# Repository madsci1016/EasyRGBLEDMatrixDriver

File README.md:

EasyRGBLEDMatrixDriver
======================

Super Easy Arduino based serial backpack driver board for 16 x 32 RGB LED Matrix panels found here: http://www.adafruit.com/products/420

The code and board  design will let you drive a 16x32 RGB LED matrix panel with a serial port, with some limitations. A example sketch for a master controller is included. 

Video Demo:  http://youtu.be/BNk5QkBuxNQ  

FEATURES:
Drive multiple panels off 1 serial port to create larger displays.

LIMITATIONS:
You only get half the resolution of the 16x32 pixel display, only 8x16 which is then scaled to 16x32
Refresh rate is limited by speed and number of displays on the Serial Port

This library runs off of an Arduino Pro/Uno which is NOT powerful enough to display video. It's really meant for animations, text, and Tetris among other things.  

In those pictures only 3 wires are shared by the 4 backpack Arduinos, 5V (Blue), GND (RED) and Data (Yellow) which is connected to the Serial RX of each Arduino (pin 1) the black wire (connected to TX of each Arduino) is not connected between each board. 

The 5th Arduino is the 'Master' and the Data line (Yellow) connects to it's Serial TX pin (Pin 0). 

Arduinos: https://www.sparkfun.com/products/11113
Wire and plug: https://www.sparkfun.com/products/9916

REQUIRES THE FOLLOWING LIBRARIES: 

https://github.com/adafruit/Adafruit-GFX-Library
https://github.com/adafruit/RGB-matrix-Panel
https://github.com/madsci1016/Arduino-EasyTransfer

To wire the display to the backpack arduino (Without my PCB), see:
https://learn.adafruit.com/32x16-32x32-rgb-led-matrix/wiring-the-16x32-matrix

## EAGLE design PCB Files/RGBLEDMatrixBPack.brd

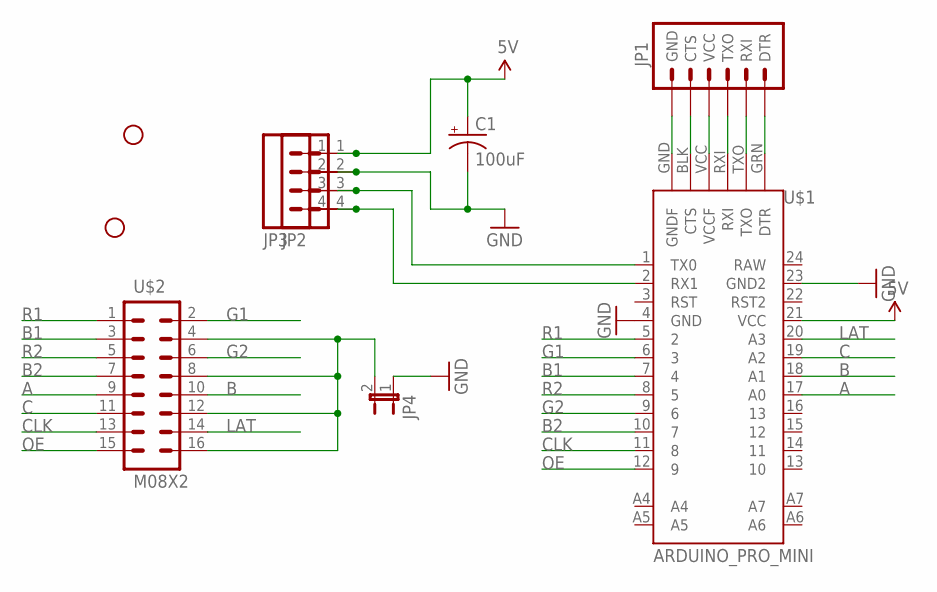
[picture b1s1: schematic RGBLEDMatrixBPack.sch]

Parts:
C1: 100uF; CPOL-RADIAL-100UF-25V
JP1: ARDUINO_SERIAL_PROGRAMPTH; 1X06
JP2, JP3: M04JST-PTH; JST-4-PTH
JP4: JUMPER-2SMD-NO; SJ_2S-NO
STANDOFF1, STANDOFF2: STAND-OFF
U$1: ARDUINO_PRO_MINI
U$2: M08X2; 2X8

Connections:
5V: C1.1 (+), JP2.1, JP3.1, U$1.21 (VCC)
A: U$1.17 (A0), U$2.9
B: U$1.18 (A1), U$2.10
B1: U$1.7 (4), U$2.3
B2: U$1.10 (7), U$2.7
C: U$1.19 (A2), U$2.11
CLK: U$1.11 (8), U$2.13
G1: U$1.6 (3), U$2.2
G2: U$1.9 (6), U$2.6
GND: C1.2 (-), JP2.2, JP3.2, JP4.1, U$1.4 (GND), U$1.23 (GND2)
LAT: U$1.20 (A3), U$2.14
unnamed: JP1.1 (DTR), U$1.GRN (DTR)
unnamed: JP1.2 (RXI), U$1.TXO
unnamed: JP1.3 (TXO), U$1.RXI
unnamed: JP1.4 (VCC), U$1.VCC (VCCF)
unnamed: JP1.5 (CTS), U$1.BLK (CTS)
unnamed: JP1.6 (GND), U$1.GND (GNDF)
unnamed: JP2.4, JP3.4, U$1.2 (RX1)
unnamed: JP2.3, JP3.3, U$1.1 (TX0)
unnamed: JP4.2, U$2.4, U$2.8, U$2.12, U$2.16
OE: U$1.12 (9), U$2.15
R1: U$1.5 (2), U$2.1
R2: U$1.8 (5), U$2.5

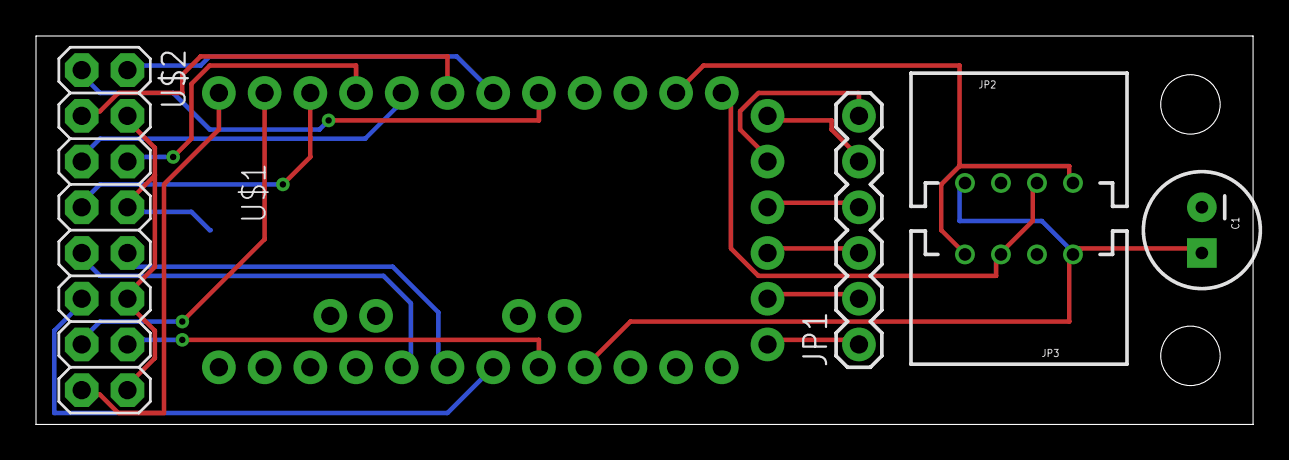
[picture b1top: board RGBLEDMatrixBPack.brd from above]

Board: 2 copper layers, 67.6 x 21.6 mm, 9 parts (1 on the bottom side), 23 nets.

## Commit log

2014-05-05 Initial Commit
    No really, the first one
2014-05-05 Forgot PCB!
    Ooops
2014-05-05 Cleaned Up ReadMe
2014-05-05 Fix Readme
2014-05-05 Grammar is not my strong suit
2014-05-05 Once more for good luck
2014-09-09 2014 RobotX Specific build Branch
    A build with custom driver specific to the 2014 RobotX Challenge.

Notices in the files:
parts and their libraries:
SparkFun-Boards: Licensing: CC v3.0 Share-Alike You are welcome to use this library for commercial purposes.
